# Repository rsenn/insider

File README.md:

## INSIDER V1.0 USER'S MANUAL

By E.E. Atanasios Melimopoulos (pic.insider@gmail.com)
(Copyright June 15 2007)

INTRODUCTION:
In-Circuit-Debuggers, as you may already know, have become the PIC’s debugging standard
tool for many programmers because it’s easy use and handy interface to the target pic-
placed-board. They come with MPLAB plug-ins that provides a full rich set of commands and
functions in order to debug your code in real time.

After hours of using some brands of ICDs, ICD2, etc. on different projects, I faced some
hardware situations where the two pin interface ICD <-> PIC becomes annoying and sometimes
difficult to work around. Apart from the fact that your target pic must run at selected
clock frequencies that allows the ICD-Uart baudrate multiplier to fit. Also, some pics do
not allow the same on-hook commands upon which ICDs are based. There is no electrical
isolation between the pic-target board and the USB–Serial PC-GND interface.

Thinking about it, I decided to build the INSIDER, based on the following:

- 1Bit Interface placed on ANY I/O selected spare pin (or carefully shared).
ICD 2bit interface is too much, usually on 12Fxxx 8-pin pics where there are only 6 I/O
pins. Also on bigger pics, like 16Fxxx and 18Fxxxx where the RB port is the most useful,
the fact that RB6-RB7 are forced to be the 2bit ICD interface, may goes against your
hardware I/O connections and sometimes you can’t share their use.
- 1Bit Interface independent of the target PIC clock speed from 20KHz to 50MHz.
ICD 2bit interface communicates to the target pic via serial ASCII link, that’s why the
pic clock freq must be close to an integer multiple of the chosen baudrate.
- 1Bit Interface independent of the target PIC type (12Fxxx, 16Fxxx, 18Fxxxx)
ICD commands and features are based on some bootstrap routines that Microchip places on
most of its MPU types. But depending of the devices class, family and generation, this
routines differs and so the ICD implementation of this functions.
- Electrical Isolation between the target PIC hardware and the PC workstation.
PICs MCU are very useful on AC-line applications where the pic floats driving a MOSFET H-
Bridge PWM converter or a Triac controlled power assembly, etc. That’s why it is so
important to isolate the PC from the Target-PIC using an isolated connection ICD tool.
- Small, easy to build, easy PC interface and very easy to use.
With a double side 1”x 2” PCB, just one 18pin dip 16F628 pic, a dual-optocoupler, leds, a
pushbutton, some resistors, serial connector, etc. I think this is a small and easy to
build circuit. With no more than 10 well designed commands and the most basic interface
available: Hyperterminal using the PC serial-Ports.

Against some opinions, PC serial comm ports are not obsolete, my Dual Core PC desktop has
two and my Core 2 Duo Laptop (HP nx6320) has one. Of course I could place an USB-Uart
bridge chip in order to use the PC USB port (maybe later) and you can find a handy PCI
card serial port for your Desktop PC. (USB-serial-port cable doesn’t work).

By now I have no time to design and build an IDE Windows interface that would allow
Symbolic cross-references to the user program to be debugged, the interface between the
INSIDER and the PC is via Hyperterminal. So, all the variables and address references to
the user program are absolute HEX, although not being so friendly because of this. At
least, the INSIDER’s Commands Set is designed to ease the HEX management as much as it was
possible. In the near future, this Command set will be the console commands upon which the
IDE windows based INSIDER Program will work (Anyone wants to help? Welcome).

This is a non-profit based project so the same is applicable to any other source of
contribution sent and shared with.
There is no responsibility to the author about any kind of damage, injuries and
consequences of any type in projects where the INSIDER will be involved.
Any feedback, contributions or modifications needed to build and IDE windows program for
the INSIDER, are welcome and you can contact me via email: pic.insider@gmail.com

## INSIDER CONCEPT:

Although some aspects of ICDs implementations, PIC Hardware Emulators, Soft Simulators,
Starter Kits, etc, has been taken into the INSIDERs design. The final implementation
differs on its actual usage; I think it will be useful to define the INSIDER tool as a
concept in order to understand its use, commands and installation.

- Real Time Debugging – That’s the big issue. No simulator available can give the same
behavior as the real thing does, apart from their bugs, most of the time it is very
difficult to simulate the in/out environment connected to your pic-target hardware.

Emulators are excellent, but you need to have expensive ic-pods for each type of pic you
may use and a complete working platform is very expensive.

In Circuit Debugger (ICD) is the best cost/performance tools available, low price, easy to
use and work in real time with your pic-target board. But they force you to leave two I/O
pins, RB6-RB7, for its interface. All pics ICD bootstrap software implementations are not
the same so all ICD’s commands are not available to all pics types. And you can’t use any
oscillator frequency except those that close fit the baudrate multiplier used in the Uart-
like pic-ICD interface.

The ICD concept relies on the strategic deployment of as many breakpoints needed in you
target pic-code, so whenever your code reach at any breakpoint, it will call and execute
the bootstrap ICD routine placed at some address outside the user code address range.

The started bootstrap ICD routine will initiate an ASCII serial communication via RB6-
with the ICD’s external hardware which handles the entire User command interface on behalf
of specially designed plug-ins on the MPLAB IDE interface upon which you can view, edit
any data, SFR register or code area, figuring out what happened with your halted code and
rerun it from the last breakpoint address or from another user selected address until the
next breakpoint is reached.

As you can see, the ICD concept is based on a carefully placement of many breakpoints
wherever it makes sense to stop/run your code giving the opportunity to review and edit
your program variables, flags, SFR contents, etc. Also, you can force any output or read
any input in order to check any interface problem with your connected hardware.
Of course ICD has more functions but the key ones are the breakpoints related.

The INSIDER concept also relies on the strategic deployment of as many breakpoints needed
in you target pic-code, but it only needs one user selected I/O pin for its interface and
it can be carefully shared with any simple input/output user connected hardware like led,
pushbutton, pull-up external input, etc. The INSIDER interface protocol is capable to
filter any I/O activity, external or from the user code, from its actual data link. Any
pic type can be used (12Fxxx, 16Fxxx, 18Fxxxx) any frequency from 20KHz to 50MHz, from VCC
3.3V to 5V.

The main difference between the INSIDER and ICD is that its pic-bootstrap routine executed
from any breakpoint must be included at the end of the user target code. Although being
small it takes up to: 160(12Fxxx), 170(16Fxxx), 400(18Fxxxx) prog-words and needs no more
than 6(12Fxxx/16Fxxx) or 7(18Fxxxx) data bytes.

The other difference is that breakpoints must be placed and flashed in the user code
source, so there is no way to clear or change them at run/debug time. But commands are
included in order to mask/unmask/trace selected breakpoints as they are debugged reducing
the times the user code must be edited/flashed to clear/insert any breakpoints. When the
user code halts at any unmasked breakpoint and after viewing-editing the pic target data
and resources, you can rerun (G cmd) the code from the halted breakpoint address or reset
you application to start again, there is no way to change the rerun address on 12Fxxx and
16Fxxx pics. But on 18Fxxxx you can change the rerun address from the halted breakpoint (G
nnnnnn cmd).

There is no opcode-trace command, INSIDERs Debug sessions relies on the strategic
deployment of up to 256 Breakpoints (00-FF break number) and its view/edit commands active
when the user code halts at any unmasked breakpoint.
But deployed breakpoints are traceable, so you can trace your code execution.

## INSIDER OPERATION:

Once you have your code written and ready to be tested on a real hardware, you will have
to insert the INSIDER’s bootstrap routine and deploy as many breakpoints as needed to
debug your code wherever it makes sense to your code logic.

There are 3 items to insert in your code, 2 macros definitions and a bootstrap routine.
Assuming an assembly code, you have to insert at your code definition start area where you
define all your variables, constants and macros, the following 2 INSIDERs macros:

DBRK EQU 1 ;This EQU will ENABLE/DISABLE(1/0) all the INSIDER items in your code.
DBEE EQU 1 ;This EQU will ENABLE/DISABLE(1/0) EEPROM-READ-CMD, If you don’t want
;or your pic doesn’t have EEPROM area, this will reduce bootstrap size

INSIDER MACRO ;INSIDER MACRO DEF, Right after the power-up reset init code, after
IF DBRK==1 ;setting up all you pics resources and variables, Placing the code
CALL DG000 ;line: INSIDER, will stop your code execution, so you can START it
ENDIF ;from the Hyperterminal interface pressing G (INSIDERs G cmd).
ENDM

BREAK MACRO bkn ;BREAK MACRO DEF, At any code line wherever you decide to place a
IF DBRK==1 ;breakpoint, you have to insert the code line: BREAK nn, where nn is
MOVWF DB0 ;the HEX number (00H-FFH) that identifies your breakpoint at the
MOVLW bkn ;Hyperterminal screen during your debugging sessions.
CALL DBUG
ENDIF
ENDM

At last, you have to place the PIC-specific Bootstrap at the end of the code memory, being
careful to do not overlap the clock calibration const usually placed at the last code-
memory address on some pics. There are 3 bootstrap routines to choose from:

18FDBUG: For 18Fxxxx pics
16FDBUG: For 16Fxxx pics
12F6DBUG: For 12F6xx pics 14Bit opcodes (like: 12F615, 12F629, 12F683, etc)

Each Bootstrap source code includes its specific MACROS and variables definitions. So you
can cut and paste them to your target code. They are carefully designed to preserve the
user’s target code environment (W, STATUS, FSR, INTCON, etc) on every breakpoint.
Once your code execution is halted by a breakpoint, The INSIDER’s commands will aid you to
view/edit the real users DATA/SFR registers contents, and any changes you made will be
reflected on the code rerun from the last breakpoint until the next one.

After saving the users INTCON value, any enabled interrupt will be masked during the
INSIDER’s execution of a breakpoint by clearing the GIE-bit in the INTCON SFR. Then
restored to the saved or user edited value when code is rerun after the breakpoint.

It is very important to define the PIC I/O-Pin-Port to be used as the INSIDER’s 1Bit
interface; this is done by setting it in the header of the respective Bootstrap routine.

Debug sessions begins by first starting Hyperterminal and configuring the PC comm port to:
38400BPS, 8Bit, 1 stop, No Parity, No Hand-Shake, ANSI, No-ECHO, Word wrap active.

Second, connect the 1Bit INSIDER’s Interface to the target selected I/O pin and GND.
Attach the INSIDER’s port to the PC-serial port, then press the INSIDER’s RESET Push
Button to make it show its start up prompt (in case it doesn’t show up automatically).

Third, power up the target board with all the INSIDER’s macros, bootstrap routine and
breakpoints included in the user code already flashed in the target pic. So your code will
start and run until it stops at the INSIDER code line waiting for the G command.

Fourth, whenever you are ready with your hardware, start your application issuing a
G command from Hyperterminal. Then your code will run until a Breakpoint is reached.

Fifth, when your code halts by a Breakpoint, The INSIDER will show you thru the
Hyperterminal screen: the Breakpoint number, WREG and STATUS contents and the PIC-freq.

Sixth, with your code halted, you can view-edit-display any DATA/SFR register.
Read/Write any port in order to check your hardware I/O.
Mask/UnMask/Trace any deployed breakpoint; view the EEPROM area, etc.

Seventh, when you are ready reviewing you PIC target variables and resources, you can
rerun your code from the last breakpoint by pressing G, rerun from other selected address
by pressing G nnnnnn (18Fxxxx only) or reset your application together with the INSIDER
and start again the debugging session. Also, depending of the errors found, you may want
to edit your code and relocate the Breakpoints and start from the beginning.

This cycle (3-7) will be repeated until all your code is debugged and works properly.

The 1Bit interface between the INSIDER and your hardware is a high impedance input; it
will never source or drain any power to the target, so you don’t need to disconnect it
from your target during its power cycle.

There are two jumpers aside the INSIDER’s DB9 port and a 9V-battery holder underneath.

When there is no battery and the jumpers are placed, the INSIDER is powered from the PC
comm port and the PC-GND is connected to your target GND (no isolation).

When there is a battery and the jumpers are not placed, the Insider is powered from the
battery and the PC-GND is NOT connected to your target GND (isolation).

The INSIDER has three operating modes:

ON-RESET: (Leds OFF)
This is the Power-up Reset state of the INSIDER. Whenever it is connected to the PC-comm
port or the Reset Pushbutton is pressed, it will be initialized and a start-up prompt
message will be shown in the user’s terminal. It would be necessary to reset the INSIDER
on those occasions when there is no connection with the target or the sync is lost due to
some debug error. Any command and breakpoint setup status are preserved, a few of the
INSIDER’s commands are available because most of them depends on the target response.

ON-SCAN: (Led Green ON)
After the INSIDER reset, there is no interaction with the target, so it must be started
issuing a G cmd. Before, the target code has been started and reached the INSIDER macro,
where it waits for the INSIDER’s G cmd to start running.
Also, after a Breakpoint, the target waits for the INSIDER’s G cmd to start running from
the Breakpoint address.
On Both situations, after executing the G cmd, the INSIDER enters to ON-SCAN mode where it
waits for a target’s breakpoint query. In this mode, the INSIDER will not respond to any
command from the User’s Terminal. Thus, the Led Green ON indicates: Target Code Run.

ON-BREAK: (Led Red ON)
This is the INSIDER’s main mode where all commands are available to the User’s terminal.
Whenever the target code reaches any enabled breakpoint address, a breakpoint query is
sent to the INSIDER making it enters to ON-BREAK mode showing the BREAK number, WREG and
STATUS contents and the pic-freq. After that, the target will wait and respond to any of
the INSIDERs debug commands issued form the User’s terminal.
On this mode, the User can view/edit all the target’s DATA/SFR area and READ/WRITE to any
of the pic’s ports in order to test any hardware interface connected to it.
Whenever the User is ready reviewing the code/DATA and decides to continue by executing G
cmd, the target code will run from the breakpoint, making the INSIDER enters ON-SCAN mode
again, until another breakpoint. Thus, the Led Red ON indicates: Target Code Stop.

## INSIDER COMMANDS:

Each time you press H from the Hyperterminal keyboard, the INSIDER will show you a quick
reference Help for the 10 commands available, each one is explained next.
For any numeric field entered like nnn sss fff dd, only the last needed digits will be
entered. For example: for nnn 345ABCD7FE001 only 001 will enter, so don’t backspace.
In case of an address range sss.fff: FE67109.CCB2FF only 109.2FF will enter.
(CR), (SP/CR), (+/-), means pressing: ENTER, SPACE or ENTER, + or -, etc.

S[T]{nnn nnn nnn}(CR)
Show Variables: The INSIDER uses hex address to reference your data. It would be useful to
store the address of the same variables you view again and again on every breakpoint.
S cmd allows you to store up to 16 nnn Hex data address to show its contents.
On any mode, Snnn nnn nnn nnn(CR) will store the entered address (up to 16).
ST will toggle AUTO ON/OFF, AUTO ON will execute S(CR) after a breakpoint query.
ON-RESET, S(CR) will only show the stored address.
ON-BREAK, S(CR) will show the s-variables contents (HEX and Binary) in the stored order.

V/X/T[N] n n n(CR)
Enable/Disable/Trace Breakpoints Groups: Breakpoints can be placed from 00H to FFH.
It would be useful to enable/disable/trace selected breakpoints as you go forward
debugging your code, this will reduce the assembly-flash-cycle of the target pic every
time you need to remove/insert breakpoints in your code. Also, you can deploy the
breakpoints by groups, for example: breakpoints 00-0FH (group-0) over the code start up,
breakpoints 10H-1FH (group-1) over the math routines, breakpoints 20H-2FH (group-2) over
the uart routine, and so on. This way by disabling group 0 and 2, only group-1 breakpoints
are allowed to halt your code in order to debug the math routines.
You can trace your code execution by tracing the deployed Breakpoints as your code pass
through them without halting but showing each breakpoint number in sequence. So, you can
see your code execution path on behalf of the fast displaying breakpoints numbers.

Executing: V2 5 3 E(CR) XA 4 1 F(CR) TD C 8 9(CR)
Will enable: 2-3-5-E, disable: 1-4-A-F, trace: 8-9-C-D break-groups at the same time.
VN(CR) enables, XN(CR) disables, TN(CR) traces -- all break-groups.
V(CR) or X(CR) or T(CR)-- will show the break-groups enable/disable/trace status.

Disabling all break-groups by XN(CR) cmd will let your code run without halting, but the
break-query is actually made on every masked breakpoint and the INSIDER will rerun your
code automatically until any User-key-press will enable the next Breakpoint.
This will add some delay on your code execution and differs from making ‘DBRK EQU 0’ in
the INSIDER bootstrap header making all INSIDERs items disappear from your code.
Tracing all break-groups by TN(CR) cmd will let your code run without halting, but on each
break-query only the breakpoint number is displayed and the INSIDER will rerun your code
automatically until any User-key-press will enable the next Breakpoint.

G{nnnnnn}(CR)
GO command: Allows you to run your code whenever you are ready with your hardware.
ON-RESET, G(CR) initiates your code execution after its power-up and the INSIDER enters
ON-SCAN mode waiting for a breakpoint query. When it occurs, the INSIDER will enter
ON-BREAK mode, where you can view/edit any DATA/SFR using the INSIDER commands.
Once you are ready to continue, you must issue G(CR) in order to rerun your code from the
last breakpoint. On pics 18Fxxxx you can specify a run address different from the last
breakpoint by issuing Gnnnnnn(CR) where nnnnnn is the address you want to run from.
On 18Fxxxx the nnnnnn address will always be forced to be even (LSBit=0).
Note that if you issue a Gnnnnnn(CR) cmd on pics type 12F6xx, 16Fxxx the target will
ignore the nnnnnn address and will run from the last breakpoint always.

N Is the same like pressing G(CR) but only works just after a Breakpoint query.
This will speed up the rerun-cycle/auto-show-variables on many successive breakpoints.

E nnn (CR) (ON-BREAK MODE ONLY)
EEPROM Dump Display: If your code uses the EEPROM DATA AREA, the ‘DBEE EQU 1’ must be set
in the INSIDER bootstrap header to enable this cmd, so you can view its contents.
E7F(CR) will display the EPROM-DATA contents, in HEX/ASCII, of your pic from 00 to 7FH.
Note that the start address is always 00H, you only specify the end address nnn.
If ‘DBEE EQU 0’, the target will ignore the command and display the DATA address only,
reducing the bootstrap size on pics without EEPROM DATA AREA or when it is not used.

D sss.fff ..sss.fff (CR) (ON-BREAK MODE ONLY)
Data Dump Display: DATA/SFR RAM address space is usually dispersed over several banks with
different sizes and gaps between address. It would be useful to display different DATA RAM
address ranges using the same command and store this ranges so they can be displayed again
without entering them each time, over and over, on every breakpoint.
D20.7F 150.166 120.135 A0.EF(CR) will display the DATA contents, in HEX/ASCII, of the
target pic from 20H to 7FH, from 150H to 166H, from 120H to 135H and from A0H to EFH.
Up to four (4) address ranges can be entered and stored in the command buffer.
So, when you press D, it will show the last address ranges used in case you want to
display them again, or just type the new address ranges to be displayed.
Note that the ASCII char of the data will be shown for values 20H-FFH, a ‘.’ for < 20H.

R nnn.nnn...nnn (SP/CR) (ON-BREAK MODE ONLY)
Read DATA/PORT: Sometimes the hardware connected to your target pic doesn’t work as you
expected. And the need arises to read at your will while you are forcing the input to do
something, like a: keyboard, encoder, A/D input potentiometer, TIMER running, etc.
On a 16F628: R5.6.1A(CR) will read the PORTA, PORTB and RCREG contents.
R6.F.E(SP) will read the PORTB, TIMER1H-L each time you press SPACE, and if you hold the
SPACE key down, the data are read continuously showing the data changing dynamically.
Up to 8 data/ports address, separated by dots, may be read in the same command.

W nnn dd (+/-/SP/CR) (ON-BREAK MODE ONLY)
Write DATA/PORT: Sometimes the hardware connected to your target pic doesn’t work as you
expected. And the need arises to write any data at your will while you are testing the
output hardware to do something, like a: LCD Display, Port expander, Stepper motor, etc.
On a 18F4620: WF82 7A(CR) will write data 7A to PORTC.
WFAD 41(SP)42(SP)43(SP)44(CR) will write ‘A’ ‘B’ ‘C’ ‘D’ to the UART-TXREG.
WF80 45(+)AA(+)(+)CF(-)73(SP)55(CR) will write 45H-AAH-CFH-73H-55H to Port A-B-D-C-C.
The (+/-) keys are used as a way to inc/dec the address pointed by the Write command.

F sss{.fff} dd dd dd (CR) (ON-BREAK MODE ONLY)
Fill DATA RAM: During a debugging session you may need to fill some RAM address range with
known data in order to verify some data process in your code.
F20.6F 00(CR) will write data 00 from 20H to 6FH.
F20.11F 12 55 43(CR) will write data 12H-55H-43H-12H-55H-43H-... from 20H to 11FH.
F20 CF 23 10 356 89FE 44(CR) will write data CFH-23H-10H-56H-FEH-44H from 20H.
Up to 16 data bytes can be used in the same cmd.
Be careful specifying the address range to do not overlap any SFR unintentionally.

B {W/S dd}(CR) (ON-BREAK MODE ONLY)
Break command: The breakpoints are only placed by inserting their macros while editing
your source code and then flashed to the target pic. But when the running code reaches to
a breakpoint and its query will set the INSIDER ON-BREAK mode, it will show you BREAK nn,
W and Status contents with the pic osc-freq and if (AUTO ON) then S(CR) will be executed.
During a debugging session, B(CR) will show the same again.
BW 7A(CR) will write 7AH to WREG. BS 03(CR) will write 03H to STATUS REG.
This edited W and STATUS values will be set on the target pic when rerun by G(CR).
This cmd allows you to edit W and STATUS without knowing their HEX address on any pic.

***************************************************************************************

Note: On any command the bootstrap target routine will not allow you to read/write over
the DB0-DB5 INSIDER bootstrap variables where the users: WREG, STATUS, INTCON, FSR (FSR0H,
FSR0L on 18Fxxxx) are preserved.
Also, whenever you point to these mentioned SFRs to edit them, the INSIDER bootstrap will
address their respective DB0-DB5 TEMPORAL-REGS to write or read from; this way the correct
user’s SFRs is preserved or edited and then restored to the target pic on rerun.

The INSIDER bootstrap routine doesn’t have any means to determine if any target address
sent by any user-command, ON-BREAK mode, exists. The user is responsible of what is
addressed on any command issued from the INSIDER and the interpretation of the data
response or effect from the target pic-hardware.

So, you can do whatever you want, if you know what you are doing.

## NOTES TIPS & HINTS:

- In order to avoid any interruption of the Target-INSIDER link during a debugging
session, you must disable the Watch Dog Timer (WDT=OFF) in case your application use it.
- Your code may use any interrupt during its execution, but whenever a breakpoint is
reached, the target INTCON value will be saved and INTCON,GIE bit will be cleared in order
to avoid any interruption of the Target-INSIDER link during the ON-BREAK mode.
You can view/edit the saved INTCON value at your will; it will only be active after the
rerun command (G cmd) when W, STATUS, FSR and INTCON are restored to the pic-target.
Note that if you have any timer interrupting your code, this timer will still be running
during the INSIDER’s ON-BREAK mode (unless you stop it by editing the TxCON SFR) and it
will not interrupt the target-pic because INTCON,GIE bit is 0. The same applies to any
peripheral’s interrupt enabled; they will be functioning but not interrupting.
You can STOP/START any peripheral before/after any selected BREAK nn to avoid losing any
code sync, overrun the UART, false ADC readings, PWM running wild, etc.
- Working with low freq-pics (<4MHz) will slow down the Target-INSIDER link speed, so if
you want a better response time of the INSIDER you can change the Speed multiplier value
defined in the Header of each bootstrap routine by increasing the DBN EQU 1 (default) to
2, 4, 8 and 16 to increase the link speed by a factor of 2x, 4x, 8x, 16x respectively.
Note that these are power of 2 values, 3, 5, 6, 10, 12, etc will not work.
- You can place (ORG) the INSIDER bootstrap routine in your code at your will; I use to
place it at the end of the last Program-Memory-Page to clearly separate it from the code
to be debugged in the Program-Memory-Usage-Map displayed in the Assembler list file. Also,
by fixing its position at any Prog-Memory page, there will be no page boundaries crossing
errors with the INSIDER bootstrap routine when linking-assembling your code.
Note that on each bootstrap routine there is an ORG ENDPROG-nnn directive where nnn is the
bootstrap length and ENDPROG is the User-Edited end-code-memory of the target pic. You
have to be careful to do not overlap any end of program OSCCAL/CONFIG Byte usually found
on many pics. So, check your pic datasheet before setting ENDPROG value.
Please don’t change the nnn value because it only defines the bootstrap length.
- INSIDERs bootstraps routines define some data-ram variables for its internal use.
On pics 12F6xx and 16Fxxx DB0-DB5 must reside in Bank-0 data RAM and DB0-DB1 must be at
Bank-0 common-access area, so they can be reached from any bank during the break-query.
On pics 18Fxxxx DB0-DB6 may be placed as a group on any data-RAM-Bank.
DB0-DB6 must be set as global variables when used to debug any C-compiled pic-code.
- INSIDER MACRO clears STATUS and W contents on 12F6DBUG and 16FDBUG bootstraps.
BREAK MACRO will preserve the user-code W, STATUS, INTCON and FSR on all bootstraps.
- Pic frequency shown at every breakpoint query has the following tolerances:
32MHz +/- 2.4% : 16MHz +/- 1.2% : 8MHz +/- 0.6% : 4MHz +/- 0.3% : 1MHz +/- 0.07%
- To debug 3.3V pic-hardware you must change the INSIDER’s (LM2936Z-5 or 78L05) to a 3.3V
regulator like LM2936Z-3.3 and resistor R8 from 750 to 430 ohms.
- INSIDER 1Bit-Interface-Pin must be defined by the user in the bootstrap header, you have
to select the Port-Bit-number and Port-Tris Reg. Note that only I/O pins will work.
The INSIDER bootstrap will set as input the selected I/O-pin 1Bit-Interface after every
breakpoint query; take it into account if you share this pin with your pic-hardware.
- In case you have to share the I/O 1Bit INSIDER connection, consider to share it with any
low importance I/O hardware like any led output, pushbutton input, etc. Where the ‘1’ and
‘0’ level will not be affected so much by the operation of the connected hardware.
The INSIDER is able to differentiate the hardware activity from its data link, but you may
notice activity in your hardware due to the INSIDER data link transfer.
If there is not any “low” importance I/O-hardware or any spare I/O pin to connect the
INSIDER. You will have to consider edit any part of your code that would allow you to free
any I/O pin for the INSIDER 1Bit Data link.
- There is no bootstrap for 12-Bit-opcodes 12F5xx pics (like: 12F509, 12F519, etc)
You can use a similar 14-Bit-opcode 12F6xx to run your (modified) 12F5xx target code.

## CIRCUIT & FILES:

In the INSIDER zip files, there are three folders:
MAIN: Contains the INSIDER_V1_628.HEX file to be flashed on the INSIDER cpu
And the INSIDER_User_manual.pdf acrobat reader file.
BOOTSTRAP: Contains the bootstrap routines for each pic family:
12F6DBUG.asm – 16FDBUG.asm – 18FDBUG.asm. And three demo sample code.
EAGLE: Contains all the Schematics and PCB files made on Eagle PCB cad, it can be
Free downloaded from [http://www.cadsoftusa.com](http://www.cadsoftusa.com) so you can edit the INSIDER circuit.

The INSIDER PCB is a 1.9” x 1.2” double layer board to be placed-glued over a 9V-battery
holder (DIGIKEY 1294K-ND) with its positive and negative legs soldered to J2 and J
connection pads on the board at each side of the DB9-female connector
The DB9-female connector is the comm-port to the PC with its wire-solder pins placed over
the edge of the board between the jumpers J2 and J3.

The Dual optocoupler MCT6 (OC1) works as the RS232 interface to the PC-comm-port and
provides an isolated high speed path to TXD and RXD PC signals biased from the PC-DTR and
GND pin. You can use other dual optocoupler as well but you have to test it and adjust R8-
9-10-11 resistors values in order to make it work at 38400BPS.
The single optocoupler OC2 will be needed by a future INSIDER IDE PC program that uses it
to reset the INSIDER with the PC-RTS signal. By now OC2 and R12 are not used.

The INSIDER’s voltage regulator (REG1) is a LM2936Z-5(TO-92) 5volt low drop-out, you can
use a 78L05. If you plan to work on 3.3v pic, replace it with a LM2936Z-3.3 and R8=430.

J1 is a 2-pin right angle pin header for the 2-wire hook-test-probes used to connect the
INSIDER J1 INS-GND to the target pic selected I/O port-pin and GND.

The INSIDER’s cpu is a 16F628 18-pin DIP with an external 20MHz parallel cut crystal.
The Bicolor led LB1 can be replaced by two leds GREEN/RED with their anodes tied to VCC.
The pushbutton T1 (DIGIKEY EG4369-ND) is used to reset the INSIDER.

The INSIDER to the PC-comm-port cable is made by connecting DB9-female 2-3-4-5 pins to a
DB9-male 2-3-4-5 pins wire connectors respectively.

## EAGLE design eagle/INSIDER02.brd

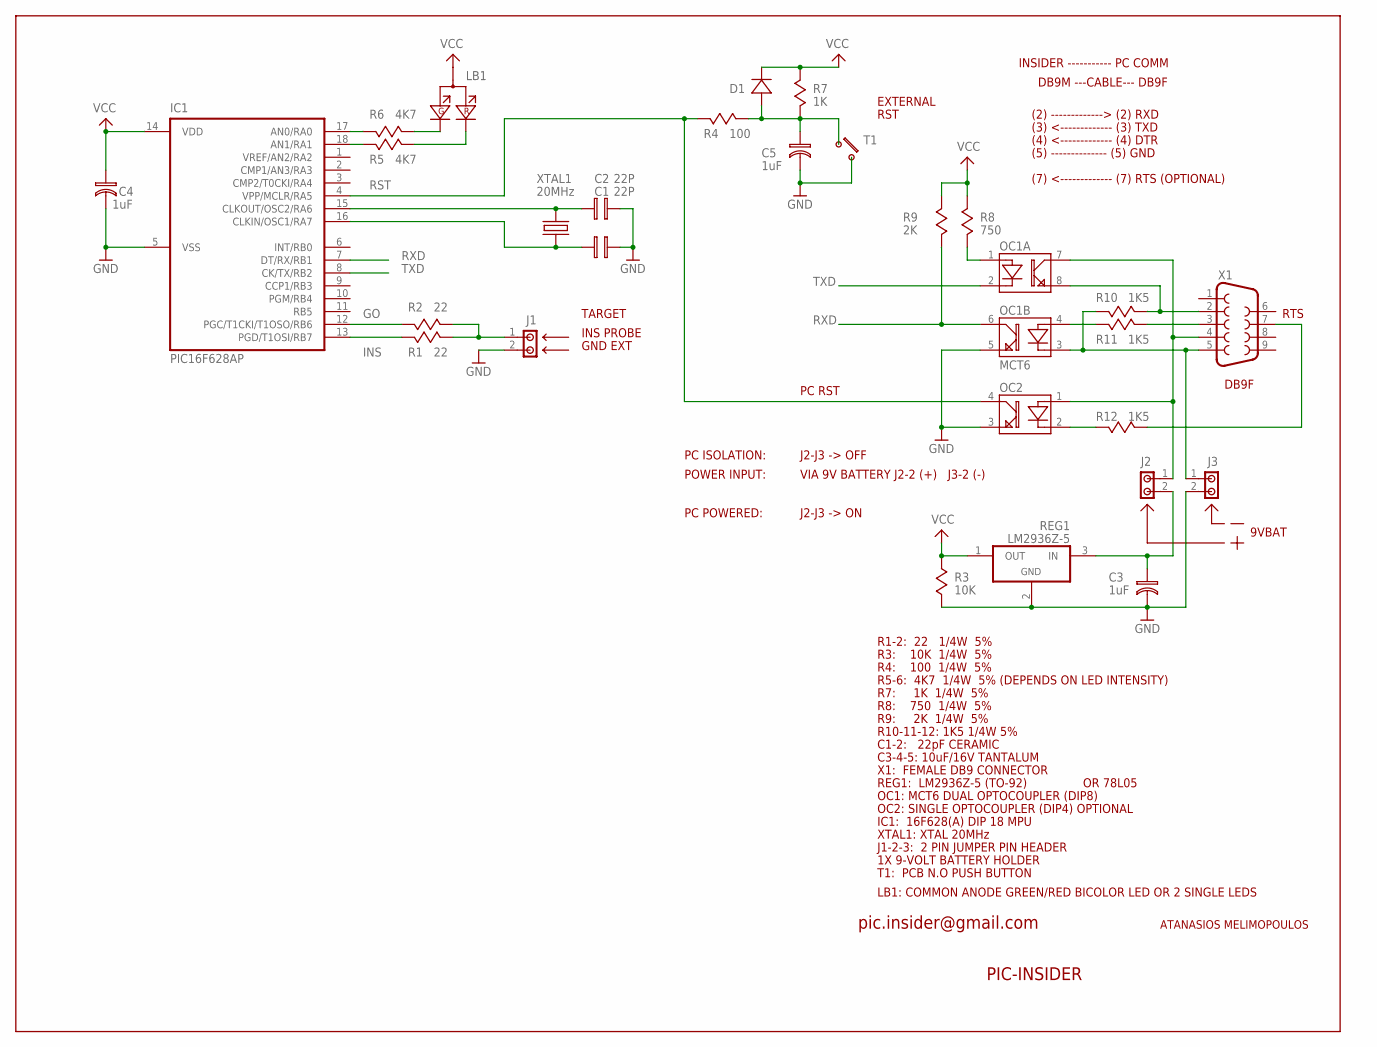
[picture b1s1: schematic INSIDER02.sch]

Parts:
C1, C2: 22P; C02
C3, C4, C5: 1uF; CP01
D1: 1N4148; D03
IC1: PIC16F628AP; DIL18
J1, J2, J3: JMP2; JP2
LB1: LEDBIAC; LEDBAC
OC1: MCT6; DIL08
OC2: OPTO1A; DIL04
R1, R2: 22; R03
R3: 10K; R03
R4: 100; R03
R5, R6: 4K7; R03
R7: 1K; R03
R8: 750; R03
R9: 2K; R03
R10, R11, R12: 1K5; R03
REG1: LM2936Z-5; TO92A
T1: TEC3; TEC3L
X1: F09D
XTAL1: 20MHz; HC49V

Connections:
GND: C1.P$2 (2), C2.P$2 (2), C3.P$2 (2), C4.P$2 (2), C5.P$2 (2), IC1.5 (VSS), J1.2, J3.2, OC1.5 (E), OC2.3 (E), R3.P$2 (2), REG1.2 (GND), T1.1
GO: IC1.12 (PGC/T1CKI/T1OSO/RB6), R2.P$2 (2)
INS: IC1.13 (PGD/T1OSI/RB7), R1.P$1 (1)
unnamed: J3.1, OC1.3 (K), R10.P$1 (1), X1.5
unnamed: OC1.8 (E), R10.P$2 (2), X1.2
unnamed: J2.1, OC1.7 (C), OC2.1 (A), X1.4
unnamed: R11.P$2 (2), X1.3
unnamed: OC1.4 (A), R11.P$1 (1)
unnamed: OC1.1 (A), R8.P$2 (2)
unnamed: OC2.2 (K), R12.P$1 (1)
unnamed: J1.1, R1.P$2 (2), R2.P$1 (1)
unnamed: C2.P$1 (1), IC1.15 (CLKOUT/OSC2/RA6), XTAL1.1
unnamed: C1.P$1 (1), IC1.16 (CLKIN/OSC1/RA7), XTAL1.2
unnamed: IC1.17 (AN0/RA0), R6.P$2 (2)
unnamed: LB1.G (K2), R6.P$1 (1)
unnamed: LB1.R (K1), R5.P$1 (1)
unnamed: IC1.18 (AN1/RA1), R5.P$2 (2)
unnamed: R12.P$2 (2), X1.7
unnamed: C5.P$1 (1), D1.P$1 (A), R4.P$1 (1), R7.P$2 (2), T1.4
unnamed: C3.P$1 (1), J2.2, REG1.3 (IN)
RST: IC1.4 (VPP/MCLR/RA5), OC2.4 (C), R4.P$2 (2)
RXD: IC1.7 (DT/RX/RB1), OC1.6 (C), R9.P$2 (2)
TXD: IC1.8 (CK/TX/RB2), OC1.2 (K)
VCC: C4.P$1 (1), D1.P$2 (K), IC1.14 (VDD), LB1.A, R3.P$1 (1), R7.P$1 (1), R8.P$1 (1), R9.P$1 (1), REG1.1 (OUT)

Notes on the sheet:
EXTERNAL
RST
PIC-INSIDER
ATANASIOS MELIMOPOULOS
9VBAT
GND EXT
INS PROBE
PC ISOLATION:
J2-J3 -> OFF
POWER INPUT:
VIA 9V BATTERY J2-2 (+) J3-2 (-)
PC POWERED:
J2-J3 -> ON
TARGET
PC RST
RTS
R1-2: 22 1/4W 5%
R3: 10K 1/4W 5%
R4: 100 1/4W 5%
R5-6: 4K7 1/4W 5% (DEPENDS ON LED INTENSITY)
R7: 1K 1/4W 5%
R8: 750 1/4W 5%
R10-11-12: 1K5 1/4W 5%
R9: 2K 1/4W 5%
C1-2: 22pF CERAMIC
C3-4-5: 10uF/16V TANTALUM
REG1: LM2936Z-5 (TO-92)
OR 78L05
OC1: MCT6 DUAL OPTOCOUPLER (DIP8)
OC2: SINGLE OPTOCOUPLER (DIP4) OPTIONAL
IC1: 16F628(A) DIP 18 MPU
XTAL1: XTAL 20MHz
J1-2-3: 2 PIN JUMPER PIN HEADER
1X 9-VOLT BATTERY HOLDER
LB1: COMMON ANODE GREEN/RED BICOLOR LED OR 2 SINGLE LEDS
X1: FEMALE DB9 CONNECTOR
(2) -------------> (2) RXD
(3) <------------- (3) TXD
(4) <------------- (4) DTR
(5) -------------- (5) GND

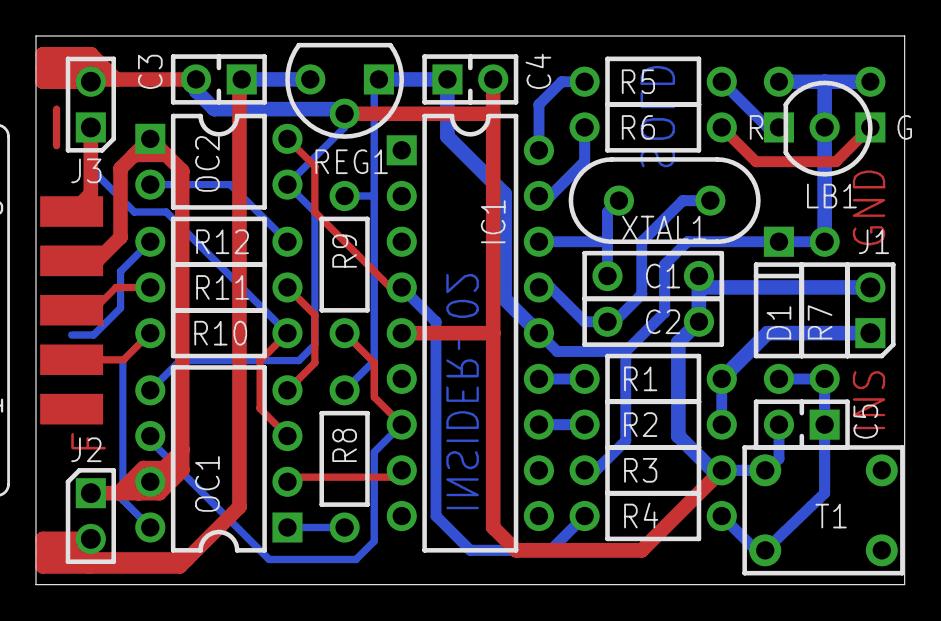
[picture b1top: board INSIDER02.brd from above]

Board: 2 copper layers, 48.3 x 30.5 mm, 29 parts (0 on the bottom side), 24 nets.
